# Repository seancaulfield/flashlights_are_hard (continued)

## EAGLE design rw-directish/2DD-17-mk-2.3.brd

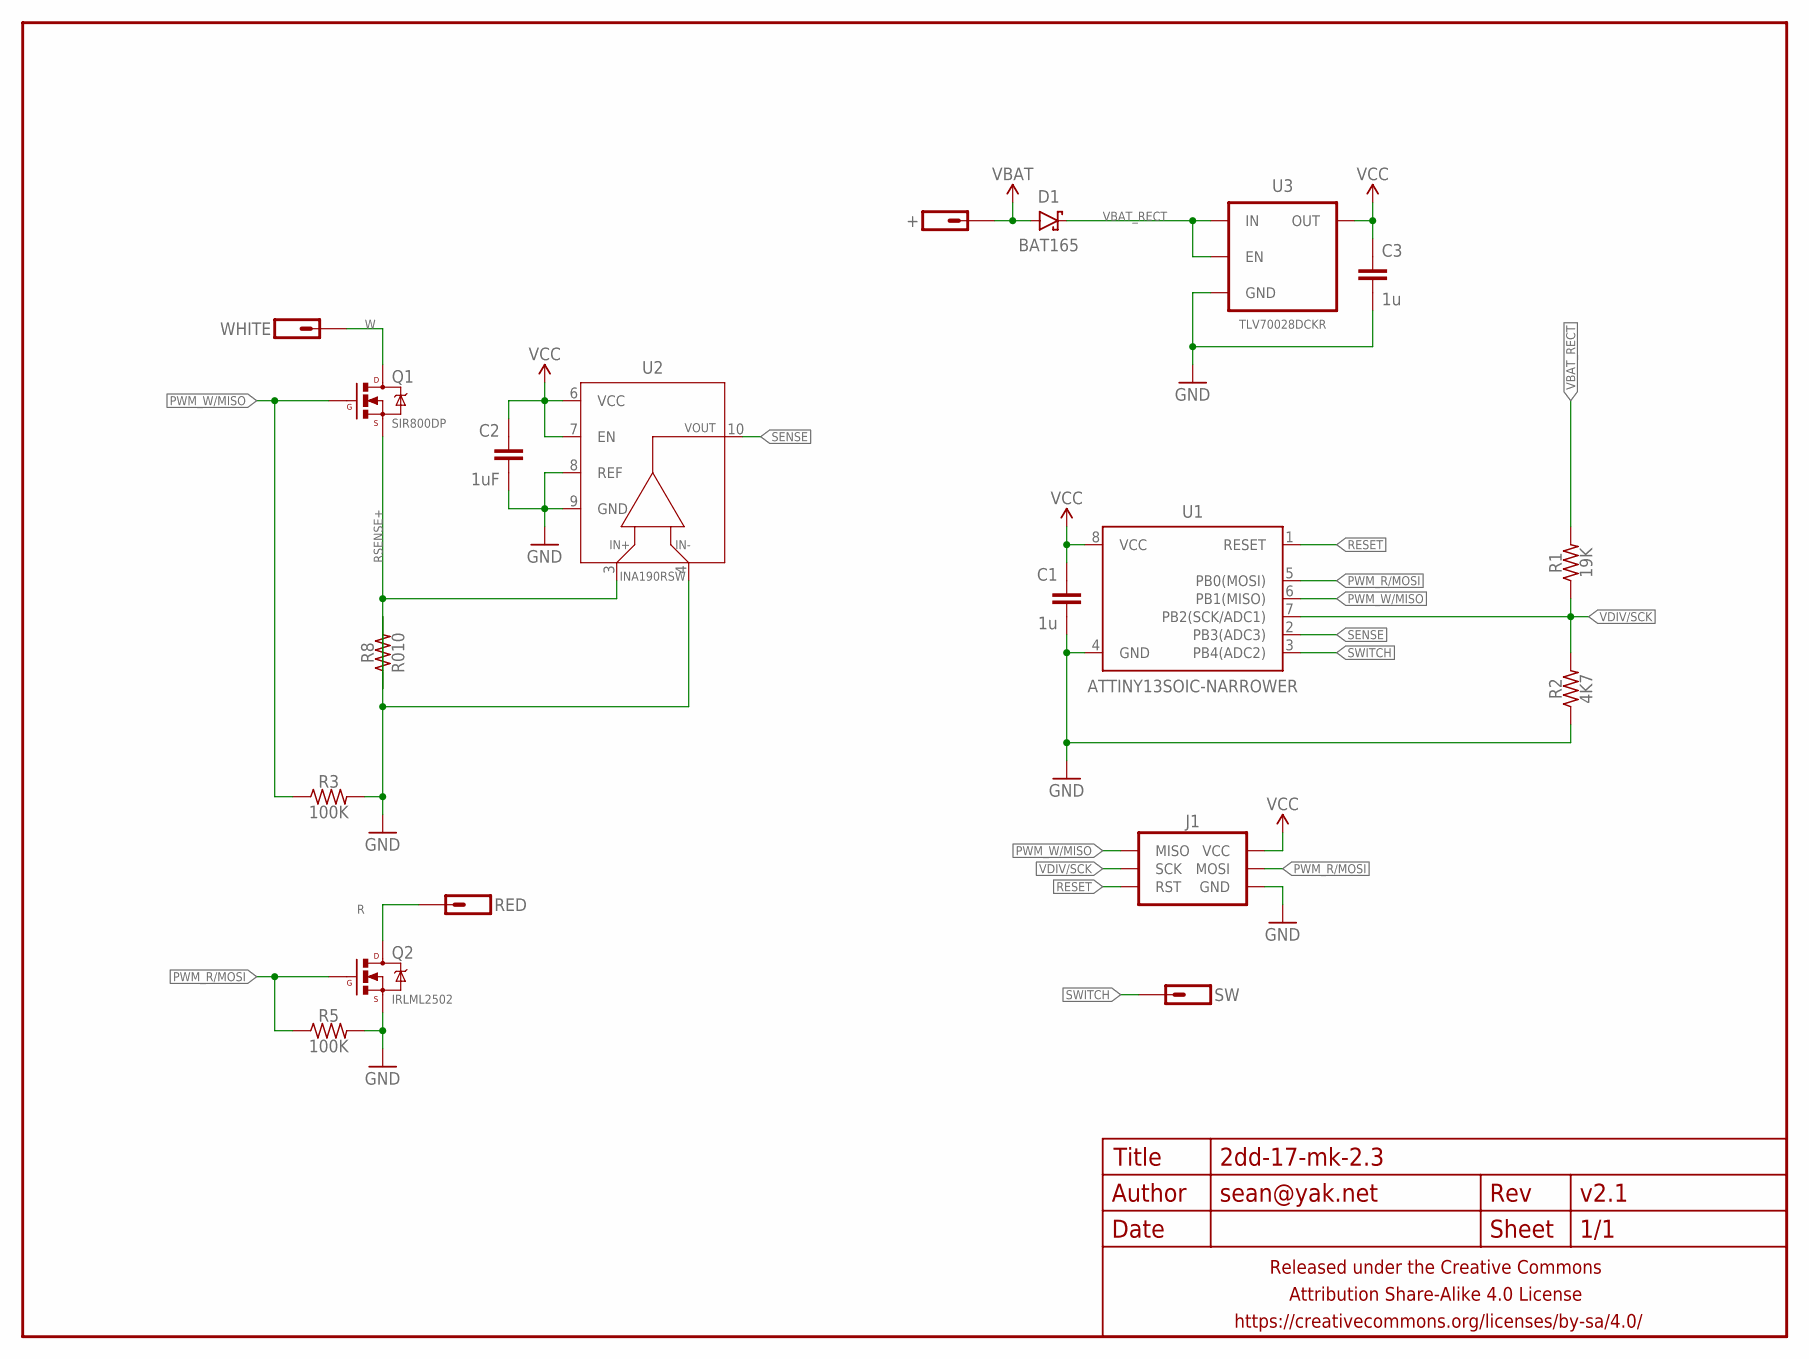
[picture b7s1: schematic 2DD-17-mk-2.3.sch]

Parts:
+: M01PTH-1MM-CIR-NS; 1X01-1MM-CIR-NS
C1, C3: 1u; C0402
C2: 1uF; C0402
D1: BAT165; SOD323-SCHOTTKY
FRAME1: FRAME-LETTERNO_PACKAGE; DUMMY
J1: AVR_SPI_PRG_6SMD-1.27MM; 2X3-1.27MM-SMD
Q1: SIR800DP; LFPAK56
Q2: IRLML2502; SOT23
R1: 19K; R0402
R2: 4K7; R0402
R3, R5: 100K; R0402
R8: R010; R1206
RED: M01SMD-1.25MM-DIA; 1X01-SMD-1.25DIA
SW: M01SMD-1.25MM-DIA; 1X01-SMD-1.25DIA
U1: ATTINY13SOIC-NARROWER; SO08-SKINNYPADS
U2: INA190RSW; UQFN-10
U3: TLV70028DCKR; SC70
WHITE: M01SMD-1.25MM-DIA; 1X01-SMD-1.25DIA

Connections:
GND: C1.2, C2.2, C3.2, J1.6 (GND), Q2.2 (S), R2.1, R3.2, R5.2, R8.2, U1.4 (GND), U2.4 (VIN-), U2.8 (REF), U2.9 (GND), U3.2 (GND)
PWM_R/MOSI: J1.4 (MOSI), Q2.1 (G), R5.1, U1.5 (PB0(MOSI))
PWM_W/MISO: J1.1 (MISO), Q1.4 (G), R3.1, U1.6 (PB1(MISO))
R: Q2.3 (D), RED.P$1
RESET: J1.5 (RST), U1.1 (RESET)
RSENSE+: Q1.1 (S), Q1.2 (S), Q1.3 (S), R8.1, U2.3 (VIN+)
SENSE: U1.2 (PB3(ADC3)), U2.10 (OUT)
SWITCH: SW.P$1, U1.3 (PB4(ADC2))
VBAT: +.1, D1.A
VBAT_RECT: D1.C, R1.2, U3.1 (IN), U3.3 (EN)
VCC: C1.1, C2.1, C3.1, J1.2 (VCC), U1.8 (VCC), U2.6 (VCC), U2.7 (EN), U3.5 (OUT)
VDIV/SCK: J1.3 (SCK), R1.1, R2.2, U1.7 (PB2(SCK/ADC1))
W: Q1.PAD (D), WHITE.P$1

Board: 2 copper layers, 20 parts (5 on the bottom side), 13 nets, no tracks yet.

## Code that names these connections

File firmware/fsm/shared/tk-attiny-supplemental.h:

/*
 * tk-attiny-supplemental.h
 *
 * Additional layout(s) for ToyKeeper's FSM framework. Separate include file to make maintenance hopefully easier.
 *
 * Copyright (C) 2018 Selene Scriven, Sean Caulfield
 *
 * This program is free software: you can redistribute it and/or modify
 * it under the terms of the GNU General Public License as published by
 * the Free Software Foundation, either version 3 of the License, or
 * (at your option) any later version.
 *
 * This program is distributed in the hope that it will be useful,
 * but WITHOUT ANY WARRANTY; without even the implied warranty of
 * MERCHANTABILITY or FITNESS FOR A PARTICULAR PURPOSE.  See the
 * GNU General Public License for more details.
 *
 * You should have received a copy of the GNU General Public License
 * along with this program.  If not, see <http://www.gnu.org/licenses/>.
 *
 */

#ifndef TK_ATTINY_SUPPLEMENTAL_H
#define TK_ATTINY_SUPPLEMENTAL_H

#ifdef _2XD_LAYOUT
#define DRIVER_TYPE_DEFINED

/*
 *           ----
 *   Reset -|1  8|- VCC
 * Eswitch -|2  7|- Voltage ADC
 *         -|3  6|- PWM (white)
 *     GND -|4  5|- PWM (red)
 *           ----
 *
 */

//#define CAP_PIN     PB3     // pin 2, OTC
//#define CAP_CHANNEL 0x03    // MUX 03 corresponds with PB3 (Star 4)
//#define CAP_DIDR    ADC3D   // Digital input disable bit corresponding with PB3

//#define PWM_PIN     PB1     // pin 6, FET PWM
//#define PWM_LVL     OCR0B   // OCR0B is the output compare register for PB1
//#define ALT_PWM_PIN PB0     // pin 5, 1x7135 PWM
//#define ALT_PWM_LVL OCR0A   // OCR0A is the output compare register for PB0

#define VOLTAGE_PIN PB2     // pin 7, voltage ADC
#define ADC_CHANNEL 0x01    // MUX 01 corresponds with PB2
#define ADC_DIDR    ADC1D   // Digital input disable bit corresponding with PB2
#define ADC_PRSCL   0x06    // clk/64

//#define AUXLED_PIN   PB4    // pin 3

#define SWITCH_PIN   PB3    // pin 2
#define SWITCH_PCINT PCINT3 // pin 2 pin change interrupt

#define PWM1_PIN PB0        // pin 5, 1x7135 PWM
#define PWM1_LVL OCR0A      // OCR0A is the output compare register for PB0
#define PWM2_PIN PB1        // pin 6, FET PWM
#define PWM2_LVL OCR0B      // OCR0B is the output compare register for PB1

#define USE_VOLTAGE_DIVIDER // use a voltage divider on pin 7, not VCC
#define VOLTAGE_PIN PB2     // pin 7, voltage ADC
#define VOLTAGE_CHANNEL 0x01 // MUX 01 corresponds with PB2
// 1.1V reference, left-adjust, ADC1/PB2
//#define ADMUX_VOLTAGE_DIVIDER ((1 << V_REF) | (1 << ADLAR) | VOLTAGE_CHANNEL)
// 1.1V reference, no left-adjust, ADC1/PB2
#define ADMUX_VOLTAGE_DIVIDER ((1 << V_REF) | VOLTAGE_CHANNEL)
#define VOLTAGE_ADC_DIDR    ADC1D   // Digital input disable bit corresponding with PB2
#define ADC_PRSCL   0x06    // clk/64

// Raw ADC readings at 4.4V and 2.2V (in-between, we assume values form a straight line)
#define ADC_44 184
#define ADC_22 92

//#define TEMP_DIDR   ADC4D
#define TEMP_CHANNEL 0b00001111

#define FAST 0xA3           // fast PWM both channels
#define PHASE 0xA1          // phase-correct PWM both channels

#endif //_2XD_LAYOUT

#endif //TK_ATTINY_SUPPLEMENTAL_H

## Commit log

2014-10-09 changing to arabic numerals for versioning and branching off board for rev2
2014-10-13 saving tinkering up to this point
2014-10-13 commit before swapping out chip tech for lm3410
2014-10-14 now with WSON LM3410 part and attiny85 chip for pwm etc
2014-10-14 tester pcb to see if this will work at all before I waste time/money etc
2014-10-19 simplified design using attiny13 SOIC footprint that's slightly smaller than the SOIC footprint for attiny85's
2014-10-19 Mucking with silkscreening/labels
2014-10-20 Turning this into a 15mm dia driver
2014-10-21 interim commit, kinda borked atm
2014-10-21 trying a compromise at 16mm dia
2014-10-21 16mm version routed and ready for fabbing
2014-10-21 Oops, forgot the stop mask for the spring >_>
2014-10-22 13mm board, which coincidently is 0.5mm too big >_<
2014-10-26 12mm driver since measurement is hard
2014-11-03 bunch of new zxld38' boards and a third revision of the lm3410 pcb
2014-11-03 rename to make naming convention and removing 13mm version b/c it was too large
2014-11-03 more renames to match convention
2014-11-03 removing 17mm board b/c of wrong size
2014-11-03 more cleanup of bad ideas
2014-11-03 branching new revision for using TSOT-23-5 version of the chip
2014-11-04 revised some more and sent to the fab the lm3410; new design based on a linear chip
2014-11-04 helps if i add the damn files
2014-11-05 boards for 9 cheap led flashlights
2014-11-06 complete pth board, already sent to fab
2014-11-10 new 20mm board and a 3 channel tester for RGB LEDs
2014-11-10 20mm linear RGB driver pcb mark 1
2014-11-10 AMC7135 linear RGB driver, since apparently i can't make up my mind which one to use
2014-11-10 revised to better deal with traces and just let the processor read the status from each (not that i really care but it means one less resistor to place)
2014-11-11 giving myself an extra 22mm in diameter and playing around with layout to see if i can get all 3 channels using this driver
2014-11-22 version two, split across two boards
2014-11-22 trying with a part i happen to have on hand (where the fuck did i get these)
2014-11-22 removing measures since they're mostly annoying
2014-11-23 faaaabulous flashlight in progress
2014-11-24 new version to split off uC from driver board and add pmosfet rev polarity protection to booster
2014-11-24 two new tries at this, about to go for 3
2014-11-25 auuuuuuuuuuuuuugh
2014-11-25 slowly making progress toward a buildable device
2014-11-28 batt con plate to smd, controller with isp using jst-zh con
2014-11-29 added #2 screw holes to each board and verified pins aligned correctly (had to flipflop 5v/gnd a few times)
2014-11-29 rerouted controller and switched to a jst-ph on top side since bottom side would hit the inductors on the booster board
2014-11-29 booster using 4x0.1in headers instead of 5x2mm, along with routing to smooth edges
2014-11-29 changed to 2.5mm drill along with 2.5mm routing all corners
2014-11-29 revised batt con plate to remove any gnd traces from near the bottom spring connector. this will mean a cobbled together 4x header for the top side, but whatever
2014-11-29 finishing touches hopefully
2014-11-29 quick fix for silkscreen overlap
2014-11-29 updating corners to 2mm curve and smoothed out curves on booster pcb
2014-12-17 slightly smaller battery connect plate
2015-01-23 simple constant current testing pcb using a NPN BJT and N-MOSFET. also ponies.
2015-01-23 theoretical attempt at a 9led driver. probably sucks.
2015-01-23 i'm not neve sure what i did here?
2015-04-16 some simple versions of shit to test out ideas
2015-04-16 unfinished design using lm3414 for driving a common anode RGB high power led
2015-04-16 the quest for more variations on a theme
2015-04-16 crazy-ass design to use common switching power chip to drive leds. can't do common anode or cathode which is a big limitation. also no idea how to calculate it for diff drive current.
2015-04-20 more boards for the pcb gods or something
2015-06-18 another board whose origin remains UNKNOWN
2017-03-31 whoa nelly lots of boards never quite finished
2017-03-31 LAZERS
2018-03-01 uncommitted pcb revs
2018-03-01 new boost converter
2018-03-09 board tweak, flashlight test program in arduino
2018-03-09 another boost controller board
2018-03-09 beginings of a red/white direct fet board
2018-03-09 everett code from BLF user of same name
2018-03-09 adding BLF-VLD driver but don't actually know what open source license it uses
2018-03-09 my own modifcation starting point
2018-03-09 whoops this one's needed from the avr-libc docs
2018-03-09 makefile changes needed to compile
2018-03-09 update ignorelist for avr-gcc
2018-03-09 attempting custom modes
2018-03-09 ok take that back test run just to be sure
2018-03-09 why no work
2018-03-09 importing https://code.launchpad.net/flashlight-firmware
2018-03-09 remove old makefile no longer in use
2018-03-11 using ToyKeeper's STAR_noinit as base
2018-03-11 this never worked...
2018-03-11 never worked so deleting
2018-03-11 minor changes for testing if things work
2018-03-11 add eeprom exptension to ignore list
2018-03-11 reformatting and adding lifepo4 build-time preproc flag
2018-03-11 add some messaging about voltage during compile
2018-03-11 add readme with history
2018-03-11 reorganize my firmwares
2018-03-11 version for ones with an OTC
2018-03-12 add fuses to upload command
2018-03-13 whoops should just use #if
2018-03-14 initial red/white led linear driver
2018-03-14 add Makefile
2018-03-14 update lifepo4 logic in driver with otc
2018-03-14 initial dual channel firmware mod
2018-03-19 r/w boards
2018-03-29 various dual channel attempts
2018-03-29 secondary channel add on board
2018-03-29 wip rgbw direct FET
2018-03-29 initial fork of startwithotc to build a X%-only driver
2018-04-14 switch moon mode off b/c i don't use much
2018-04-14 attempting LM3410 boost setup for liefpo4
2018-04-14 various direct drivers wip
2018-04-14 whoops these are 20mm not 17mm
2018-04-28 different sized boards for mp3412
2018-04-28 added RST pullup because wat
2018-04-28 more layout changes
2018-04-28 keep me from bricking any more attiny85s with bad fuse settings you moron
2018-04-29 initial dual channel momentary firmware in arduino
2018-04-29 initial branch of rampingios to see if i can get it to do what i want
2018-05-22 remove unneeded build files
2018-06-06 strictly linear two channel driver
2018-06-12 more linear wip
2018-06-18 make fuse setting less dangerous
2018-06-18 more 17mm board revisions
2018-06-22 20mm dual channel linear driver
2018-06-22 attempt at uc regulated CC LED driver for convoy l4
2018-06-23 renaming for what thye actually are
2018-06-23 fix silk
2018-06-23 more renaming
2018-06-23 remove the not-gonna-bother charger design
2018-06-23 rename 17mm linear driver boards
2018-06-23 these never went to the fab
2018-06-23 redundant fiels
2018-06-23 more cleanup
2018-06-23 rename linear boards
2018-06-24 fix cream layer for stencils
2018-06-24 24mm linear dual driver
2018-07-03 wip 2DD-20 Mk 2 based on attiny84 qfn package
2018-07-03 minor tweaks to STAR forks
2018-07-15 slightly larger supplemental linear driver board with slightly larger holes
2018-07-16 Alfredo, flashlight driver based on the spaghetti monster framework from ToyKeeper
2018-07-28 increase power path diode to sod123
2018-07-28 some other LED chips
2018-07-28 apparently i'm really into this hobby
2018-07-28 more wip
2018-08-30 new switch boards and fuse tweak
2018-08-30 initial import and rearrangement for updating to r213
2018-08-30 add in my hardware defs
2018-09-01 eswitch driver with temp control fork
2018-09-02 basic FSM momentary driver from TK
2018-09-02 formatting
2018-09-02 remove bricking fuse settings you dumbass
2018-09-02 since avrdude keeps core dumping on me
2018-09-30 whoops left these here?
2018-10-08 wip multiple attiny targets
2018-10-08 make compile for attiny25
2018-10-08 sync up makefiles
2018-10-08 switch attiny13 fuses for 4.8MHz F_CPU
2018-11-03 wip for aux boards
2018-11-28 many WIP, left side
2019-01-01 bunch of new board word
2019-01-01 mtn-max driver from rmm for testing
2019-01-01 minor compile warning changes
2019-01-05 new buckboost hardware design
2019-01-20 wip: adding prescaler contorl
2019-01-21 switch board with more secure battery holder
2019-01-21 no idea if i'll actually use these
2019-01-21 whole bunch of crap in here
2019-01-21 testing TPS63020 dimming
2019-01-25 more wip buck-boost hardware
2019-01-28 wip boost mp3431
2019-02-03 more mp3431 wip
2019-02-03 branching firmware for TPS63020 driver
2019-02-03 Revert prescaler ctrl to go back to "stock" STARwithOTC
    This reverts commit 265b2a3dc185f89113ba7715350690c82de46743.
2019-02-04 making my own pogo adapter
2019-02-04 correct ADC thresholds for LiFePO4
2019-02-16 wip buck boost
2019-02-16 change to working fuses for no OTC
2019-03-09 new revision w/o opamp
2019-03-09 poor mans wattsup clone, SPICE modeling
2019-03-09 new bom for gxb172 rev1
2019-10-17 allow programmer definition via var
